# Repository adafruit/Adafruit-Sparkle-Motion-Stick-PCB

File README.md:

## Adafruit Sparkle Motion Stick - WLED-friendly USB Stick PCB

<a href="http://www.adafruit.com/products/6332"><br/>
Click here to purchase one from the Adafruit shop</a>

PCB files for the Adafruit Sparkle Motion Stick - WLED-friendly USB Stick. 

Format is EagleCAD schematic and board layout
* https://www.adafruit.com/product/6332

### Description

The Adafruit Sparkle Motion Stick is part of our series of "Sparkle Motion" boards, which are our attempt to make the best small WLED-friendly smart LED driving board in the whole world. Our resident mermaid, firepixie makes a lot of projects with WLED, and she loves it! So, how can we make something powerful enough to drive advanced LED projects that need a compact design?

The USB Stick version of the Sparkle Motion is a simpler version of our full-featured Sparkle Motion. It even fits into a low cost off-the-shelf case for protection. Please note the case is not included with this product, so don't forget to pick one up if you want it in a case!

* Power via USB Type A for up to 5V 2A input - you can use off-the-shelf USB battery packs for portable operation.
* 2 Amp resetting fuse to protect from over-current drive
* ESP32 mini module with built-in antenna port - the classic ESP32 has the best WLED support, even if we'd prefer the 'S2 or 'S3. Comes with 4 MB of flash, dual-core 240MHz Tensilica, WiFi, Bluetooth LE, and Bluetooth Classic support.
* USB-serial converter with auto-reset
* Two output signals plus 5V power and ground - both signal outputs are level shifted to 5V.
* Built-in I2S microphone for audio-reactive projects
* Built-in Infrared receiver on GPIO 10 for easy remote control integration
* User button on GPIO 0 which you can press even when its in the snap-on case
* Red built-in LED on pin 4
* Small built-in NeoPixel on pin 18
* Screw terminal blocks for no-solder connectivity

Compared to our larger Sparkle Motion board, this only supports 5V and doesn't have a reset button, there are fewer outputs, and no breakout pads of I2C/GPIO connections for external accessories.
Compared to our Sparkle Motion Mini, this has a USB A port so it's 2A max power. It does have IR and built-in terminal blocks but does not have GPIO breakout pads.

While we recommend it for use with WLED, it will also work just fine as a compact ESP32 board for use with Arduino, ESP-IDF, MicroPython, CircuitPython, or any other ESP32-supported codebase. 

### License

Adafruit invests time and resources providing this open source design, please support Adafruit and open-source hardware by purchasing products from [Adafruit](https://www.adafruit.com)!

Designed by Limor Fried/Ladyada for Adafruit Industries.

Creative Commons Attribution/Share-Alike, all text above must be included in any redistribution. 
See license.txt for additional details.

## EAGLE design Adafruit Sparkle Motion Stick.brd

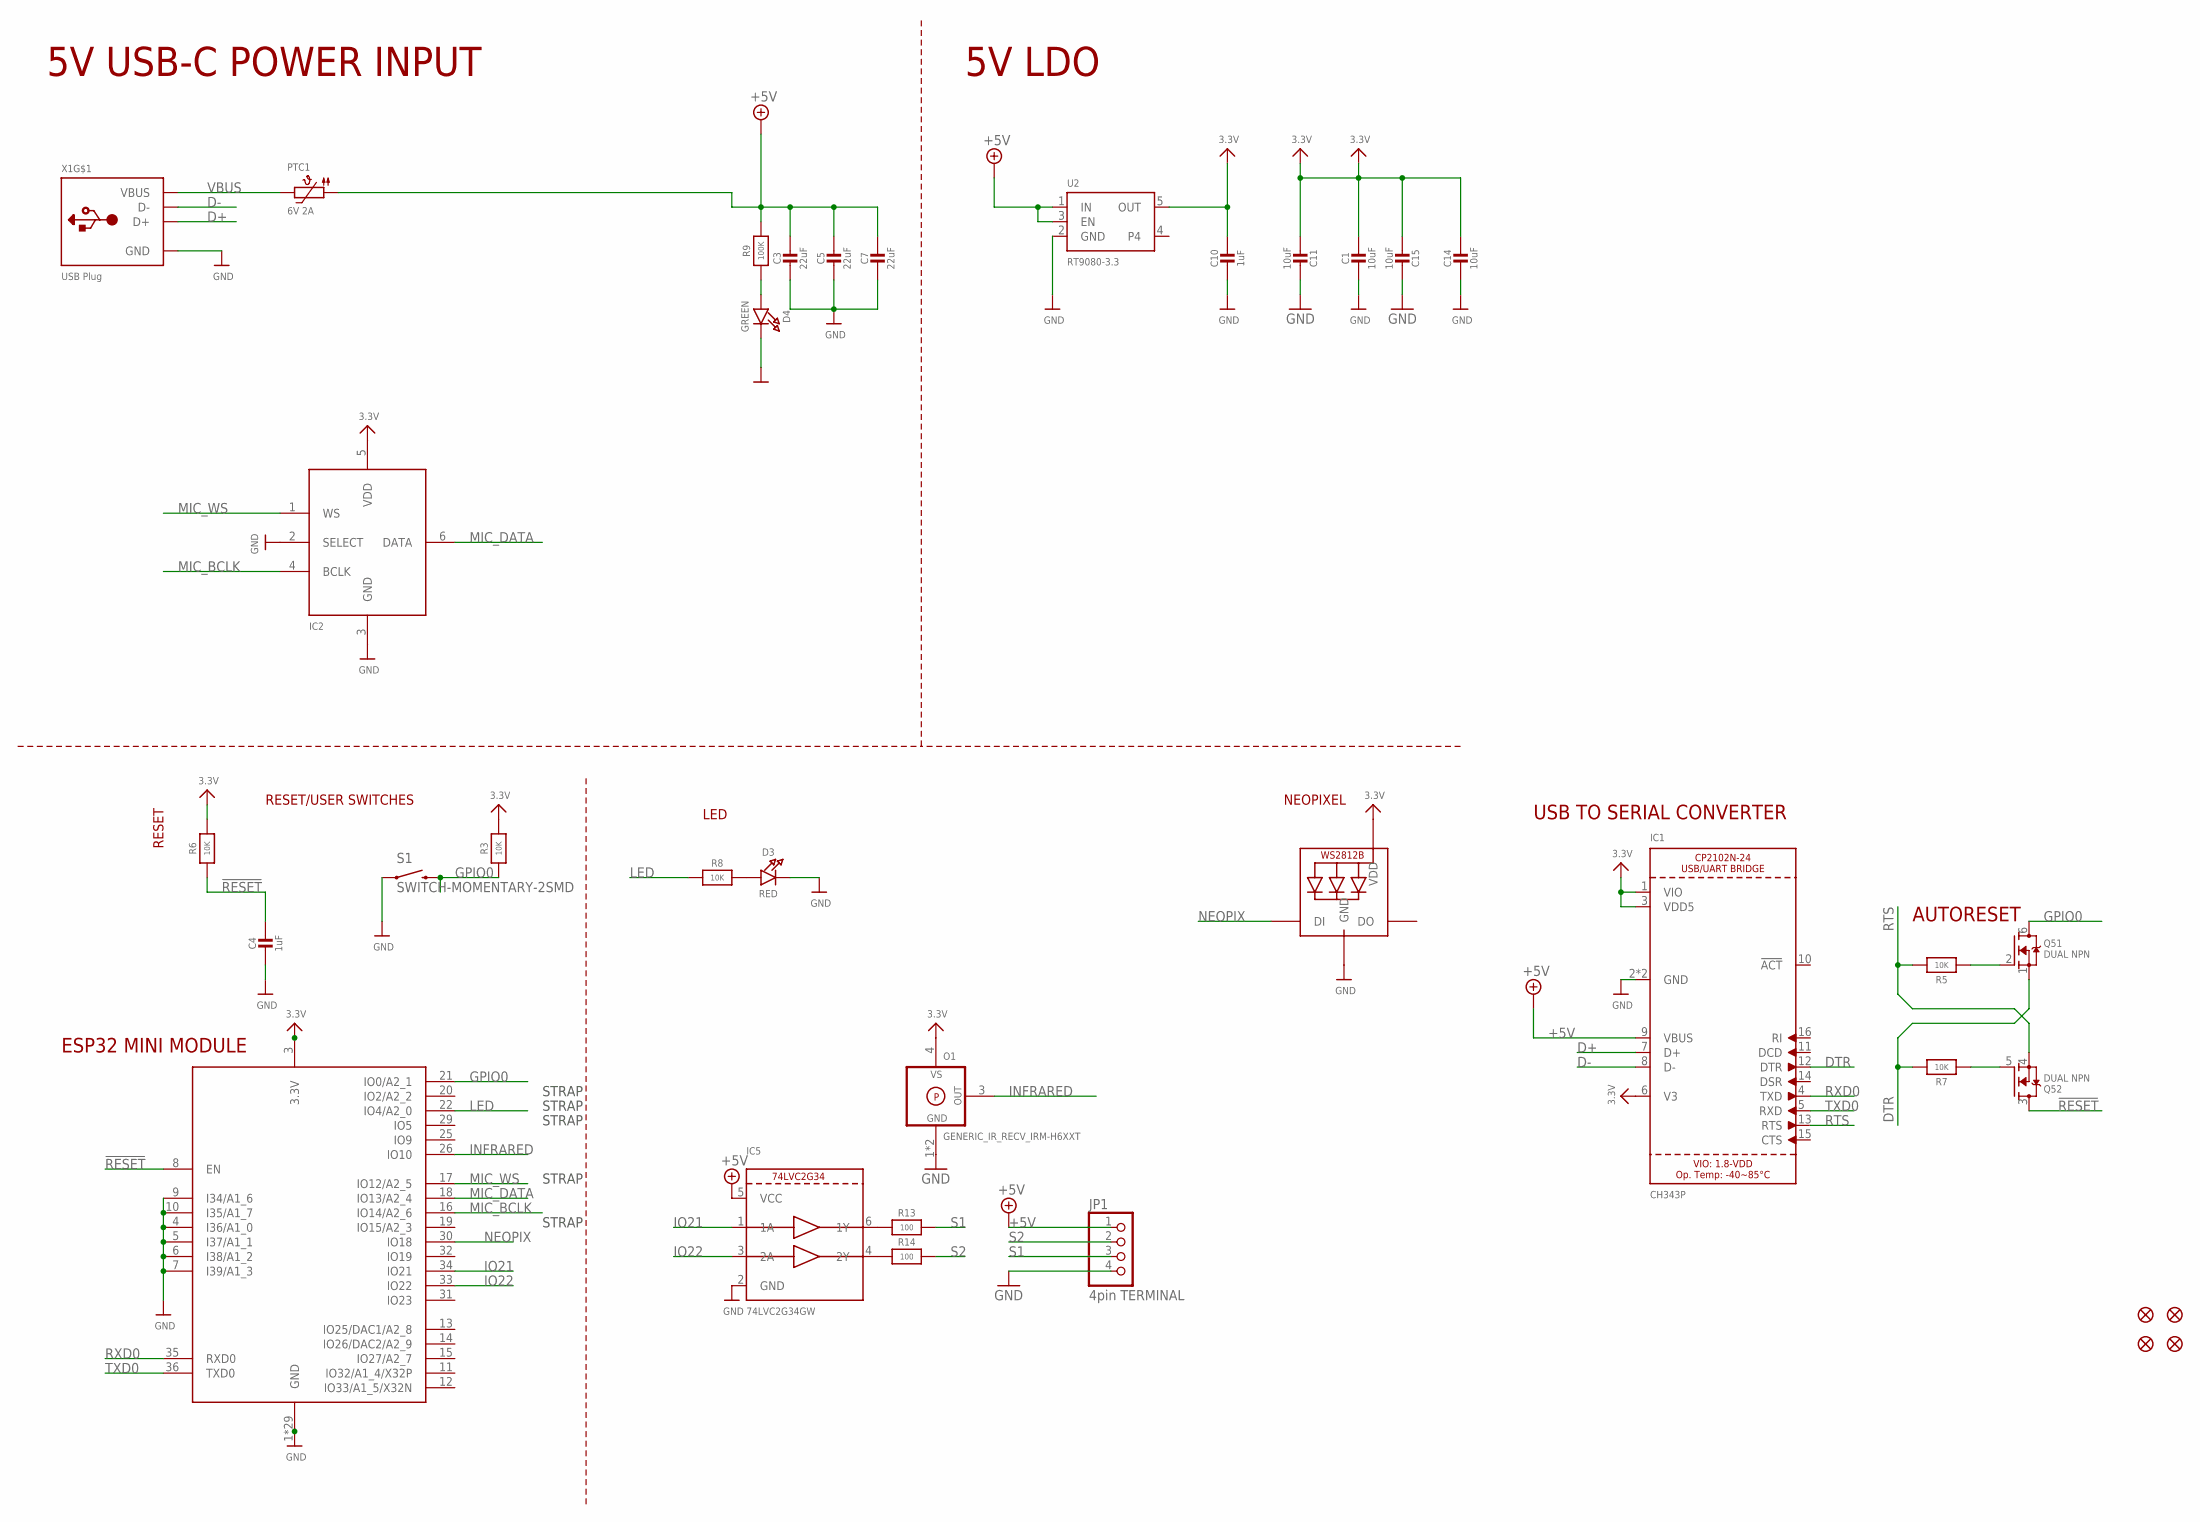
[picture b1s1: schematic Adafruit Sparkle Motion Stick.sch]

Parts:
C1, C11, C14, C15: 10uF; 0805-NO
C3, C5, C7: 22uF; 0805-NO
C4, C10: 1uF; 0603-NO
D3: RED; CHIPLED_0603_NOOUTLINE
D4: GREEN; CHIPLED_0603_NOOUTLINE
IC1: CH343P; QFN16_3MM
IC2: ICS-43434; SPH0645LM4H
IC5: 74LVC2G34GW; SC70-6L
JP1: 4pin TERMINAL; 1X04_2.54MMTERMINAL
LED1: WS2812B_SK6805_1515; SK6805_1515
O1: GENERIC_IR_RECV_IRM-H6XXT; IRM-H6XXT
PTC1: 6V 2A; 0805-NO
Q5: DUAL NPN; SOT363; JLC_ROTATION 90
R3, R5, R6, R7, R8: 10K; 0603-NO
R9: 100K; 0603-NO
R13, R14: 100; 0603-NO
S1: SWITCH-MOMENTARY-2SMD; TACTILE_SWITCH_SMD
U2: RT9080-3.3; SOT23-5; JLC_ROTATION 0
U$23, U$25, U$34, U$35: FIDUCIAL_0.5MM
X1: USB Plug; USB_A-UGO4DD
X4: ESP32-MINI-1

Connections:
3.3V: C1.1, C10.1, C11.1, C14.1, C15.1, IC1.1 (VIO), IC1.3 (VDD5), IC1.6 (V3), IC2.5 (VDD), LED1.2 (VDD), O1.4 (VS), R3.2, R6.2, U2.5 (OUT), X4.3 (3.3V)
!RESET: C4.1, Q5.3 (D), R6.1, X4.8 (EN)
+5V: C3.1, C5.1, C7.1, IC1.9 (VBUS), IC5.5 (VCC), JP1.1, PTC1.1, R9.2, U2.1 (IN), U2.3 (EN)
D+: IC1.7 (D+), X1.D+
D-: IC1.8 (D-), X1.D-
DTR: IC1.12 (DTR), Q5.1 (S), R7.2
GND: C1.2, C3.2, C4.2, C5.2, C7.2, C10.2, C11.2, C14.2, C15.2, D3.C, D4.C, IC1.2 (GND), IC1.THERMAL (GND), IC2.2 (SELECT), IC2.3 (GND), IC5.2 (GND), JP1.4, LED1.4 (GND), O1.1 (GND), O1.2 (GND), S1.1, U2.2 (GND), X1.GND, X4.1 (GND), X4.2 (GND), X4.4 (I36/A1_0), X4.5 (I37/A1_1), X4.6 (I38/A1_2), X4.7 (I39/A1_3), X4.9 (I34/A1_6), X4.10 (I35/A1_7), X4.27 (GND), X4.38 (GND), X4.39 (GND), X4.40 (GND), X4.41 (GND), X4.42 (GND), X4.43 (GND), X4.44 (GND), X4.45 (GND), X4.46 (GND), X4.47 (GND), X4.48 (GND), X4.49 (GND), X4.50 (GND), X4.51 (GND), X4.52 (GND), X4.53 (GND), X4.54 (GND), X4.55 (GND), X4.56 (GND), X4.57 (GND), X4.58 (GND), X4.59 (GND), X4.60 (GND), X4.61 (GND), X4.62 (GND), X4.63 (GND)
GPIO0: Q5.6 (D), R3.1, S1.3 (2), X4.21 (IO0/A2_1)
INFRARED: O1.3 (OUT), X4.26 (IO10)
IO21: IC5.1 (1A), X4.34 (IO21)
IO22: IC5.3 (2A), X4.33 (IO22)
LED: R8.1, X4.22 (IO4/A2_0)
MIC_BCLK: IC2.4 (BCLK), X4.16 (IO14/A2_6)
MIC_DATA: IC2.6 (DATA), X4.18 (IO13/A2_4)
MIC_WS: IC2.1 (WS), X4.17 (IO12/A2_5)
unnamed: D3.A, R8.2
unnamed: D4.A, R9.1
unnamed: Q5.5 (G), R7.1
unnamed: Q5.2 (G), R5.1
unnamed: IC5.6 (1Y), R13.1
unnamed: IC5.4 (2Y), R14.1
NEOPIX: LED1.1 (DI), X4.30 (IO18)
RTS: IC1.13 (RTS), Q5.4 (S), R5.2
RXD0: IC1.4 (TXD), X4.35 (RXD0)
S1: JP1.3, R13.2
S2: JP1.2, R14.2
TXD0: IC1.5 (RXD), X4.36 (TXD0)
VBUS: PTC1.2, X1.VBUS

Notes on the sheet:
5V USB-C POWER INPUT
RESET
LED
NEOPIXEL
ESP32 MINI MODULE
RESET/USER SWITCHES
AUTORESET
USB TO SERIAL CONVERTER
5V LDO
STRAP

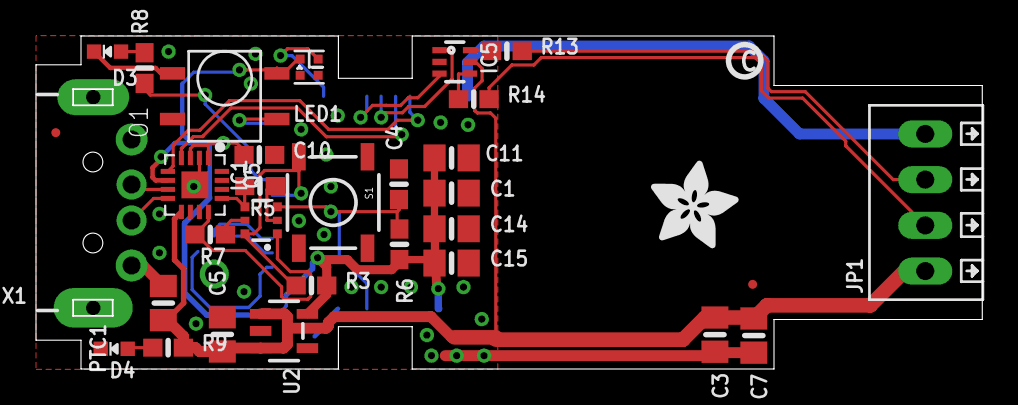
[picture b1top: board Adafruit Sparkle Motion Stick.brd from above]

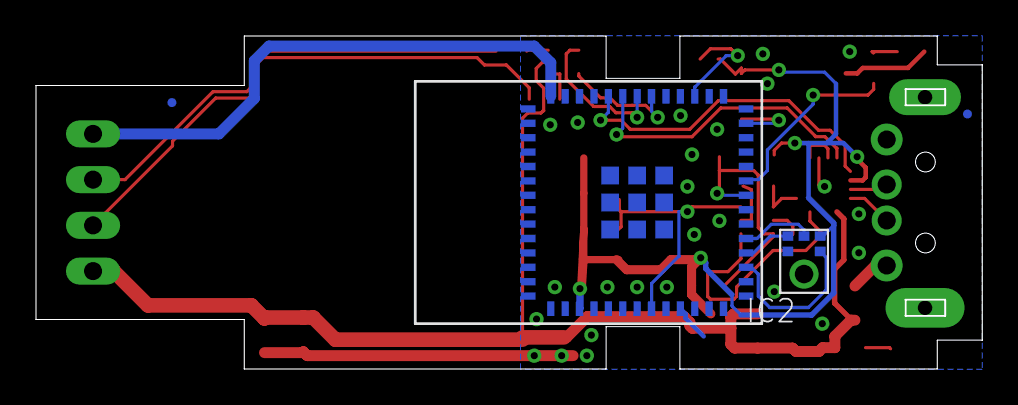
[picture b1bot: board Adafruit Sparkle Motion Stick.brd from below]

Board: 2 copper layers, 52.5 x 18.4 mm, 59 parts (11 on the bottom side), 28 nets.

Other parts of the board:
E$1: ADAFRUIT_5MM
PLABEL0: PLABEL0
PLABEL1: PLABEL1
PLABEL2: PLABEL2
PLABEL3: PLABEL3
PLABEL4: PLABEL4
PLABEL5: PLABEL5
PLABEL6: PLABEL6
PLABEL7: PLABEL7
PLABEL8: PLABEL8
PLABEL9: PLABEL9
PLABEL10: PLABEL10
PLABEL11: PLABEL11
PLABEL12: PLABEL12
PLABEL13: PLABEL13
PLABEL14: PLABEL14
PLABEL15: PLABEL15
PLABEL16: PLABEL16
PLABEL17: PLABEL17
PLABEL18: PLABEL18
PLABEL19: PLABEL19
PLABEL20: PLABEL20
PLABEL21: PLABEL21
U$10: PCBFEAT-REV-040

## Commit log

2025-05-14 cookiecutter
2025-05-16 prettypins
2025-05-21 update ir_rx to ir label

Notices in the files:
parts and their libraries:
microbuilder: This work is placed in the public domain, and may be freely used for commercial and non-commercial work with the following conditions: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
SparkFun: Licensing: CC v3.0 Share-Alike You are welcome to use this library for commercial purposes.
